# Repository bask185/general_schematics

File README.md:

General schematics and PCB designs

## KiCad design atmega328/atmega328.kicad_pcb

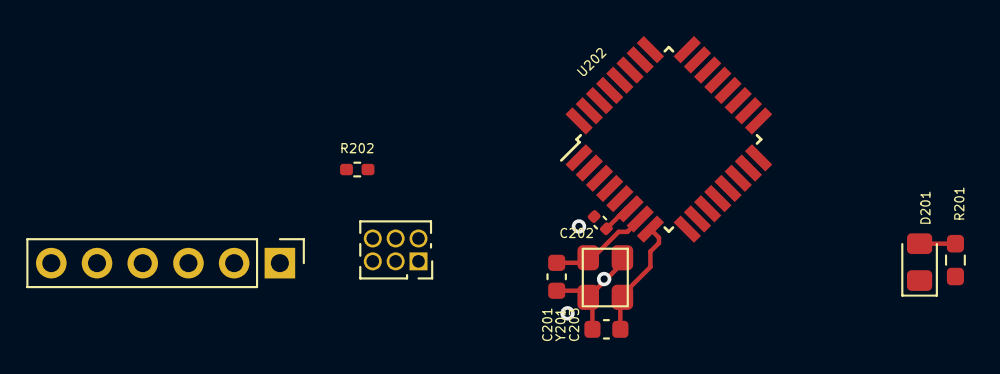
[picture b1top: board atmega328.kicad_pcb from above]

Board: 2 copper layers, 10 parts (0 on the bottom side), 9 nets.

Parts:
C201, C203: 12pF; C_0603_1608Metric
C202: 100nF; C_0402_1005Metric
D201: LED; LED_0805_2012Metric_Pad1.15x1.40mm_HandSolder
J201: HEADER_3x2; PinSocket_2x03_P1.27mm_Vertical
J202: ICSP; PinHeader_1x06_P2.54mm_Vertical
R201: 6k2; R_0603_1608Metric_Pad0.98x0.95mm_HandSolder
R202: 10k; R_0402_1005Metric_Pad0.72x0.64mm_HandSolder
U202: ATmega328-A; TQFP-32_7x7mm_P0.8mm
Y201: Crystal_GND2; crystal_arduino

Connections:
+5V: C202.1, J201.5, R201.1, R202.1, U202.4 (VCC), U202.6 (VCC), U202.18 (AVCC)
/LED: D201.1 (K), J201.4, J202.3, U202.17 (PB5)
/MISO: J201.6, J202.4, U202.16 (PB4)
/MOSI: J201.3, J202.5, U202.15 (PB3)
/Reset: J201.2, J202.2, J202.6, R202.2, U202.29 (~RESET/PC6)
/X1: C201.2, U202.7 (XTAL1/PB6), Y201.1
/X2: C203.2, U202.8 (XTAL2/PB7), Y201.3
GND: C201.1, C202.2, C203.1, J201.1, J202.1, U202.3 (GND), U202.5 (GND), U202.21 (GND), Y201.2 (GND), Y201.4 (GND)
unnamed: D201.2 (A), R201.2

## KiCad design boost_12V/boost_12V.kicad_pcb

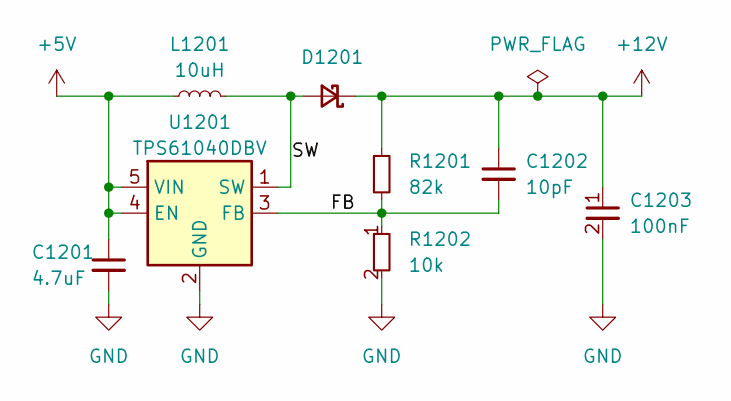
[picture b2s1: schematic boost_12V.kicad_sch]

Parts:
C1201: 4.7uF; C_0603_1608Metric; JLCPCB Part# C19666
C1202: 10pF; C_0603_1608Metric; JLCPCB Part# C1634
C1203: 100nF; C_0603_1608Metric; JLCPCB Part# C14663
D1201: D_Schottky_Small; D_SMA; JLCPCB Part# C2480
L1201: 10uH; L_1206_3216Metric; JLCPCB Part# C395029
R1201: 82k; R_0603_smalltext; JLCPCB Part# C23254
R1202: 10k; R_0603_smalltext; JLCPCB Part# C25804
U1201: TPS61040DBV; SOT-23-5; JLCPCB Part# C7722

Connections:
+5V: C1201.1, L1201.1, U1201.4 (EN), U1201.5 (VIN)
+12V: C1202.1, C1203.1, D1201.1 (K), R1201.1
/FB: C1202.2, R1201.2, R1202.1, U1201.3 (FB)
/SW: D1201.2 (A), L1201.2, U1201.1 (SW)
GND: C1201.2, C1203.2, R1202.2, U1201.2 (GND)

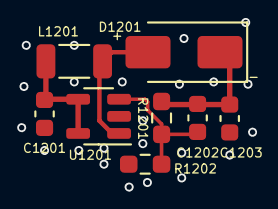
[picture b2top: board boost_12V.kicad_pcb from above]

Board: 2 copper layers, 8 parts (0 on the bottom side), 5 nets.

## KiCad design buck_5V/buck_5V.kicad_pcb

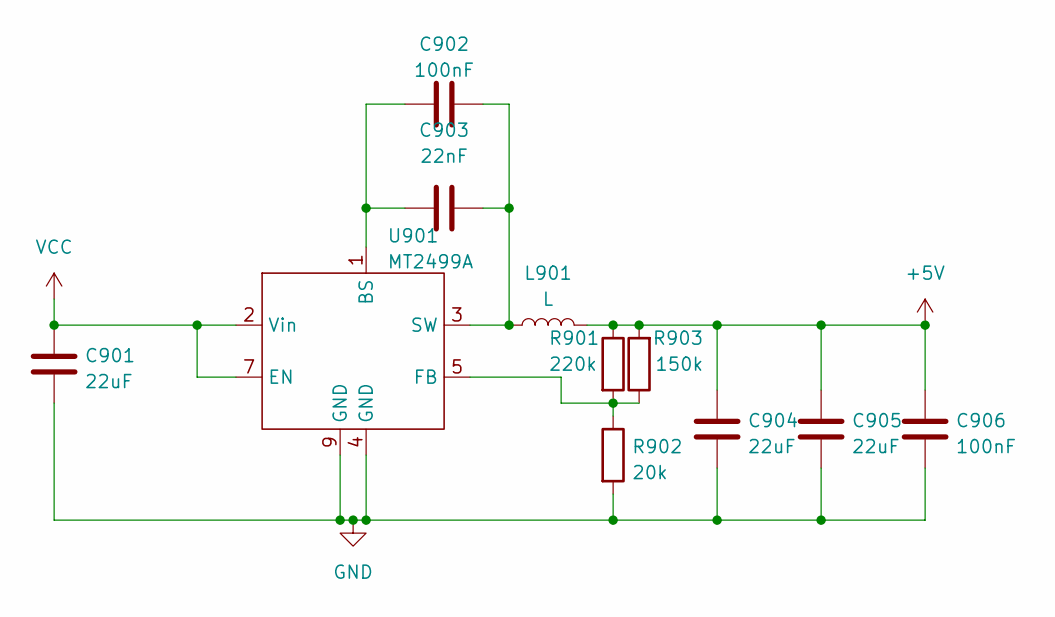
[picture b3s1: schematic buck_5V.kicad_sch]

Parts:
C901, C904, C905: 22uF; C_0603_1608Metric; JLCPCB Part# C45783
C902, C906: 100nF; C_0402_1005Metric; JLCPCB Part# C307331
C903: 22nF; C_0402_1005Metric; JLCPCB Part# C1532
L901: L; L_Bourns-SRN8040_8x8.15mm; JLCPCB Part# C92945
R901: 220k; R_0603_1608Metric; JLCPCB Part# C22961
R902: 20k; R_0603_1608Metric; JLCPCB Part# C4328
R903: 150k; R_0603_1608Metric; JLCPCB Part# C22807
U901: MT2499A; TI_SO-PowerPAD-8; JLCPCB Part# C3007555

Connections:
+5V: C904.1, C905.1, C906.1, L901.2, R901.1, R903.2
GND: C901.2, C904.2, C905.2, C906.2, R902.2, U901.4 (GND), U901.9 (GND)
unnamed: C902.1, C903.1, U901.1 (BS)
unnamed: R901.2, R902.1, R903.1, U901.5 (FB)
unnamed: C902.2, C903.2, L901.1, U901.3 (SW)
VCC: C901.1, U901.2 (Vin), U901.7 (EN)

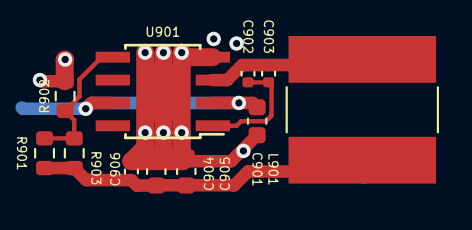
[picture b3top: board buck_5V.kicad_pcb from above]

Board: 2 copper layers, 11 parts (0 on the bottom side), 6 nets.

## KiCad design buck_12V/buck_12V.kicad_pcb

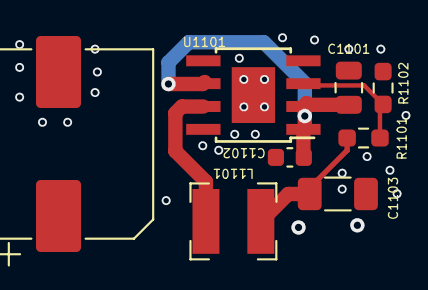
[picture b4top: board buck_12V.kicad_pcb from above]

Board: 2 copper layers, 8 parts (0 on the bottom side), 5 nets.

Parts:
C1101: 4.7uF; C_0805_2012Metric
C1102: 100nF; C_0603_1608Metric
C1103: 22uF; C_1206_3216Metric_Pad1.33x1.80mm_HandSolder
C1104: 470uF; CP_Elec_10x10
L1101: 3.3uH; L_Bourns-SRN4018
R1101: 22k; R_0603_1608Metric_Pad0.98x0.95mm_HandSolder
R1102: 1k5; R_0603_1608Metric_Pad0.98x0.95mm_HandSolder
U1101: ST1S10PHR; TI_SO-PowerPAD-8

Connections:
/12V: C1103.1, C1104.1, L1101.2, R1101.1
/GND: C1101.2, C1102.2, C1103.2, C1104.2, R1102.2, U1101.4 (AGND), U1101.5 (SYNC), U1101.8 (PGND), U1101.9 (PADGND)
/Vin: C1101.1, C1102.1, U1101.1 (VINA), U1101.2 (INH), U1101.6 (VINSW)
unnamed: R1101.2, R1102.1, U1101.3 (FB)
unnamed: L1101.1, U1101.7 (SW)

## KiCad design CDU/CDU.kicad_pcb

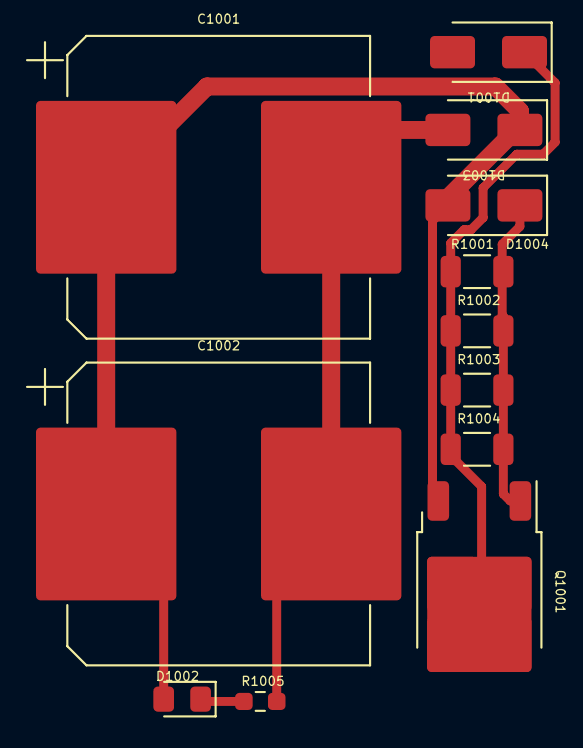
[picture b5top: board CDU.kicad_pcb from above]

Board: 2 copper layers, 12 parts (0 on the bottom side), 5 nets.

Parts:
C1001, C1002: 1000uF; CP_Elec_16x17.5
D1001, D1003, D1004: D; D_SMA
D1002: LED; LED_0805_2012Metric_Pad1.15x1.40mm_HandSolder
Q1001: 4A_DARLINGTON; TO-252-2
R1001, R1002, R1003, R1004: 2k; R_1206_smalltext
R1005: 1k; R_0603_smalltext

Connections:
/AC2(-): C1001.2, C1002.2, D1003.2 (A), R1005.2
/OUT+: D1004.1 (K), Q1001.1 (B), R1001.2, R1002.2, R1003.2, R1004.2
unnamed: D1001.1 (K), Q1001.2 (C), R1001.1, R1002.1, R1003.1, R1004.1
unnamed: C1001.1, C1002.1, D1002.2 (A), D1003.1 (K), D1004.2 (A), Q1001.3 (E)
unnamed: D1002.1 (K), R1005.1

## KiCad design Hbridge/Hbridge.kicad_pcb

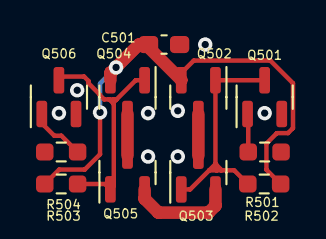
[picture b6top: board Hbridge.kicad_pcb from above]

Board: 2 copper layers, 11 parts (0 on the bottom side), 9 nets.

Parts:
C501: 100nF; C_0603_1608Metric_Pad1.08x0.95mm_HandSolder
Q501, Q506: BC847; SOT-23
Q502, Q504: P-channel; SOT-23
Q503, Q505: N-channel; SOT-23
R501, R504: 1k; R_0603_smalltext
R502, R503: 10k; R_0603_smalltext

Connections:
/CurrentSense: Q503.2 (S), Q505.2 (S)
/GND: C501.1, Q501.2 (E), Q506.2 (E)
/OUT_A: Q502.3 (D), Q503.3 (D)
/OUT_B: Q504.3 (D), Q505.3 (D)
/Vin: C501.2, Q502.2 (S), Q504.2 (S), R502.1, R503.1
unnamed: Q501.1 (B), R501.2
unnamed: Q501.3 (C), Q502.1 (G), Q503.1 (G), R502.2
unnamed: Q504.1 (G), Q505.1 (G), Q506.3 (C), R503.2
unnamed: Q506.1 (B), R504.1

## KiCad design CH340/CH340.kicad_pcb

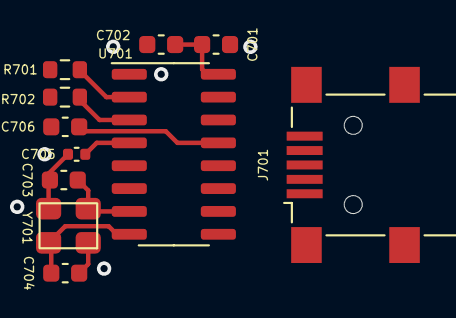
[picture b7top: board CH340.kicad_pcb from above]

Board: 2 copper layers, 11 parts (0 on the bottom side), 10 nets.

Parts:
C701: 10uF; C_0603_1608Metric
C702, C706: 100nF; C_0603_1608Metric
C703, C704: 22pF; C_0603_1608Metric
C705: 100nF; C_0402_1005Metric
J701: USB_B_Mini; USB_Mini-B_Lumberg_2486_01_Horizontal
R701, R702: 1k; R_0603_1608Metric
U701: CH340G; SOIC-16_3.9x9.9mm_P1.27mm
Y701: Crystal; crystal_arduino

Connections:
/5V: C701.1, C702.1, J701.1 (VBUS), U701.16 (VCC)
/GND: C701.2, C702.2, C703.2, C704.2, C705.1, J701.5 (GND), J701.6 (Shield), U701.1 (GND), Y701.2 (GND), Y701.4 (GND)
unnamed: J701.3 (D+), U701.5 (UD+)
unnamed: J701.2 (D-), U701.6 (UD-)
unnamed: R702.2, U701.3 (RXD)
unnamed: R701.1, U701.2 (TXD)
unnamed: C705.2, U701.4 (V3)
unnamed: C703.1, U701.7 (XI), Y701.1
unnamed: C704.1, U701.8 (XO), Y701.3
unnamed: C706.1, U701.13 (~DTR)

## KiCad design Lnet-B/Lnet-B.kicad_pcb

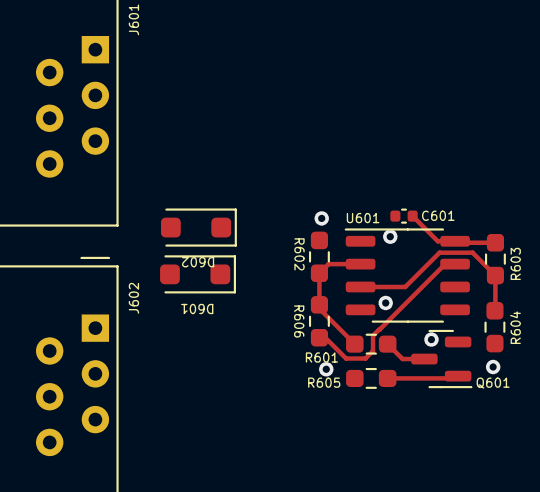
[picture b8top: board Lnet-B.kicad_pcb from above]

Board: 2 copper layers, 13 parts (0 on the bottom side), 10 nets.

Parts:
C601: 100nF; C_0402_1005Metric
D601, D602: SM4007; D_SOD-123F
J601, J602: RJ12
Q601: BC847; SOT-23
R601: 47k; R_0603_smalltext
R602: 150k; R_0603_smalltext
R603: 10k; R_0603_smalltext
R604: 22k; R_0603_smalltext
R605: 1k; R_0603_smalltext
R606: 220k; R_0603_smalltext
U601: LM311; SOP-8_3.9x4.9mm_P1.27mm

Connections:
/5V: C601.1, R603.1, U601.8 (V+)
/12V: D601.1 (K), D602.1 (K)
/GND: C601.2, J601.2, J601.5, J602.2, J602.5, Q601.2 (E), R602.2, R604.1, U601.1 (GND), U601.4 (V-)
/Lnet_Rx: R606.2, U601.7
unnamed: Q601.1 (B), R605.1
unnamed: J601.3, J601.4, J602.3, J602.4, Q601.3 (C), R601.1
unnamed: R601.2, R602.1, R606.1, U601.2 (+)
unnamed: R603.2, R604.2, U601.3 (-)
railsyncA: D602.2 (A), J601.6, J602.6
railsyncB: D601.2 (A), J601.1, J602.1

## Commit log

2023-01-09 made additions to the project
2023-01-11 added missing schematics
2023-02-24 added ch340.sch
2023-02-24 added eeprom.sch
2023-04-03 changed some stuff to ch340 and Lnet B
2023-04-05 added decoupling capacitor to atmega schematic
2023-04-06 minor update with partnumbers and footprints
2023-07-06 added hierarchial labels to some schematics
2023-08-21 moved some schematic scheets to their own folders and routed a board with it. This allow for re-use of PCB parts.
2023-09-12 added CDU with SMD parts and hierarchial sheet
2023-11-14 changed incorrect LCSC numbers for the 5V buck converter. The inductor and a capacitor had wrong footprints. Also removed all fp-info-cache files
2024-02-09 removed hierarchial labels for power symbols and replaced them with actual power symbols also updated footprint of the inductor of the 5V buck
2024-02-09 also updated 12v buck converter with power symbols
2024-02-21 added 12V boost converter (300mA max!)
2024-06-06 added design rules
2024-06-06 made some hierarchial label changes and updated atmega328
